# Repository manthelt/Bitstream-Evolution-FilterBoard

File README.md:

# Bitstream-Evolution-FilterBoard
Logan Manthey Spring 2023-2024

<!-- markdown-toc start - Don't edit this section. Run M-x markdown-toc-refresh-toc -->
**Table of Contents**

- [Bitstream-Evolution-FilterBoard](#bitstream-evolution-filterboard)
    - [Purpose](#purpose)
    - [Use](#use)
        - [Scope](#scope)
        - [Ardunio Nano](#ardunio-nano)
    - [Filter](#filter)
        - [Testing the Filter](#testing-the-filter)
            - [Results of the Filter Plus Software Modifications](#results-of-the-filter-plus-software-modifications)
    - [BOM](#bom)
    - [Future Work](#future-work)
        - [Notes for Next Revisions](#notes-for-next-revisions)
            - [FPGA Header Placement](#fpga-header-placement)
            - [Through Hole Parts](#through-hole-parts)
    - [Current Timeline](#current-timeline)

<!-- markdown-toc end -->

## Purpose
This board is a simple header board to be able to mount an FPGA, Ardunio Nano Microcontroller, and as ESPOtek Labador to it. This board also includes a basic passive low pass filter which will filter measurements on the ardunio to be more accurate to what we can accurately gather it will also ensure consistency with how we are gathering measurements as well. This PCB also allows us to test fit headers for future boards to build as well. 

|  | 
|:--:| 
| *Populated PCB* |

|  | 
|:--:| 
| *Unpopulated PCB* |

|  | 
|:--:| 
| *PCB Render* |

## Use

### Scope
The following scope was used in this project. To find further documentation about both software and how to use the scope take a look at this link.
[EspoTek Link](https://espotek.com/labrador/)

### Ardunio Nano
Given this board has some filtering on it there needs to be some slight modification to the ReadSignal.ino file that has been used in the past. These modifications include filtering out values which are outside of the range of testing. To start I had this value just at 10K so basically filtering out any values below 10K which would include both values beyond what the nano can read and some that the nano can read. This will ensure that the only values sent back to the computer will be accurate values. Further testing to adjust this value may be required and will be updated in later revisions. See the below section [Testing the Filter](### Testing the Filter) for more infomation about finding this value.

## Filter
The filter used has a 160 ohm resistor and a 0.01 uF capacitor this gives a -3dB cutoff frequency of 99471.8394 Hz. In testing at 3.3 volts this will give us an accurate interrupt reading range on the ardunio of between 10kHz and 60Khz with only some aliasing around the 55kHz to 60Khz range. This is much better than not using as there will be aliasing anywhere above about 100kHz whereas this will simply just filter those values out. Though this is an extremly simple filter it will allow us to ensure that our measurements we are getting are in a certain measureable range while still maintaining affordability. During some initial testing of this I found that the max value we could accurately measure with the interrupt counter was at about 60Khz.

|  | 
|:--:| 
| *Bode Plot* |

|  | 
|:--:| 
| *Step Response* |

### Testing the Filter
To test the filter the following configuration on the board was used. 

|  | 
|:--:| 
| *Filter Testing Setup* |

In short the signal generator was connected to the port where the FPGA signal is normally coming from and this is then connected to the ardunio nano through the PCB as normal. The scope section was connected as normal as well to monitor the filter.

#### Results of the Filter Plus Software Modifications

## BOM

| Part                        | Quanity |
| --------------------------- | ------- |
| 160 Ohm Resistor            | 1       |
| 0.01 uF Capacitor           | 1       |
| 10 Pin 2.54mm Female Header | 3       |
| 15 Pin 2.54 Female Header   | 2       |

## Future Work

### Notes for Next Revisions
#### FPGA Header Placement
Due to measuring with a ruler the pin placement is less than ideal. Getting better measurements using a caliper instead should fix this in the next revision. 

#### Through Hole Parts
I wasn't quite a fan of how the through hole parts fit with the footprints that I had. This isn't a huge issue but may want to fix for the next revision of this board.     

## Current Timeline
This board is a part of a series of more iterative and rapid prototyping boards rather than a complete all encompassing board. This is the first in that series which is meant to test the specifics of the pulse count experiment. 

- [x] Revision 1
- [ ] Revision 1.1
  - Fix FPGA Header Placement

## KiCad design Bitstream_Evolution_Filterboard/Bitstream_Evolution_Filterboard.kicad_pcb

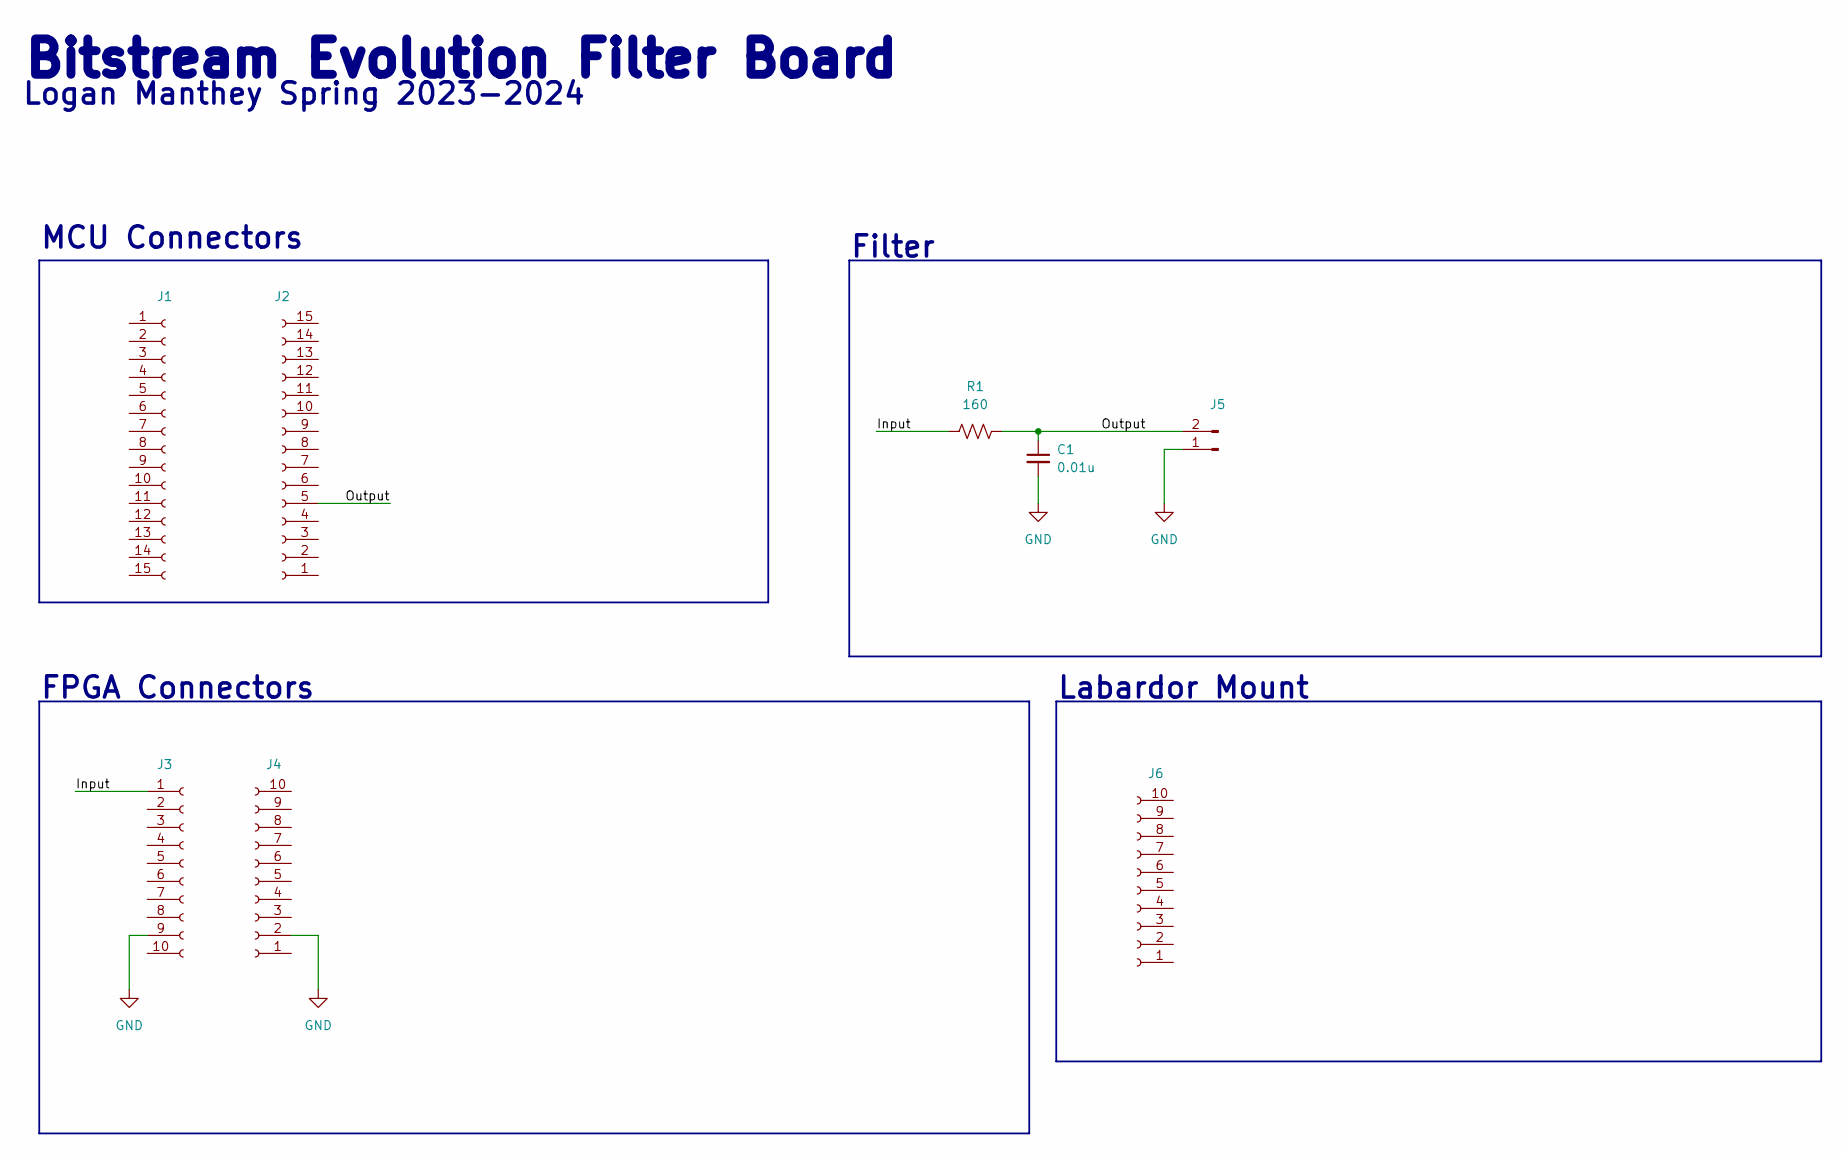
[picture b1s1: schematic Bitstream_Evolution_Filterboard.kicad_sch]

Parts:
C1: 0.01u; C_Axial_L3.8mm_D2.6mm_P7.50mm_Horizontal
J1, J2: Conn_01x15_Female; PinSocket_1x15_P2.54mm_Vertical
J3, J4, J6: Conn_01x10_Female; PinSocket_1x10_P2.54mm_Vertical
J5: Conn_01x02_Male; PinSocket_1x02_P2.54mm_Vertical
R1: 160; R_Axial_DIN0204_L3.6mm_D1.6mm_P7.62mm_Horizontal

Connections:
/Input: J3.1, R1.1
/Output: C1.1, J2.5, J5.2, R1.2
GND: C1.2, J3.9, J4.2, J5.1

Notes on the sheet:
Filter
Logan Manthey Spring 2023-2024
FPGA Connectors
Labardor Mount
MCU Connectors
Bitstream Evolution Filter Board

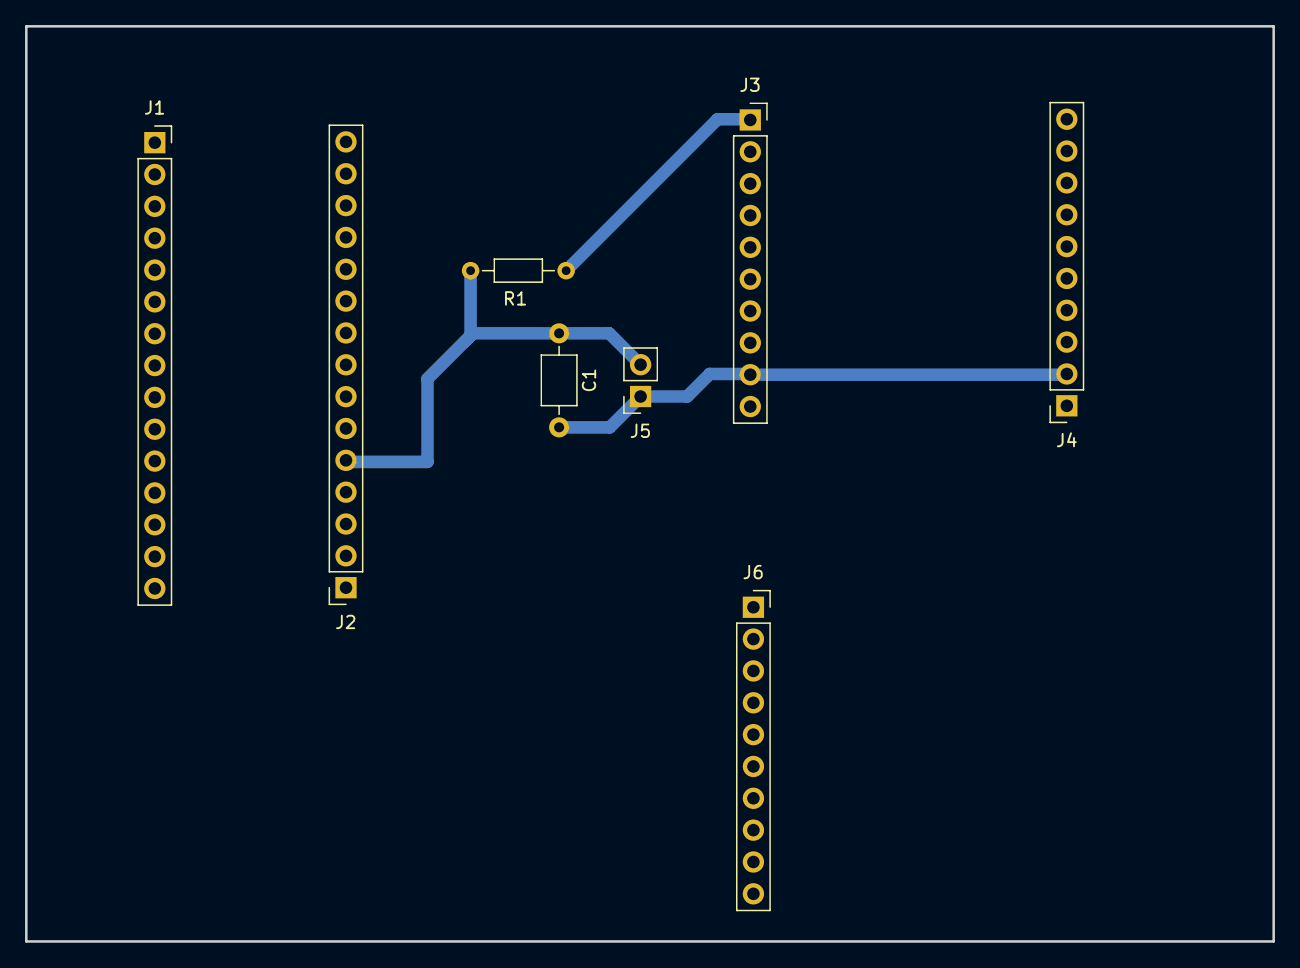
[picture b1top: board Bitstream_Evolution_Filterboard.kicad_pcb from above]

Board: 2 copper layers, 99.5 x 73.0 mm, 8 parts (0 on the bottom side), 3 nets.

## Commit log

2024-04-16 Started Work
2024-04-17 Updates to Hardware
2024-04-17 Sent out PCB
2024-04-17 Updates to Readme.md
2024-04-19 Updated Pictures
2024-04-19 Updates to Readme, Determined I need to swap caps
2024-04-19 Updates to Readme
